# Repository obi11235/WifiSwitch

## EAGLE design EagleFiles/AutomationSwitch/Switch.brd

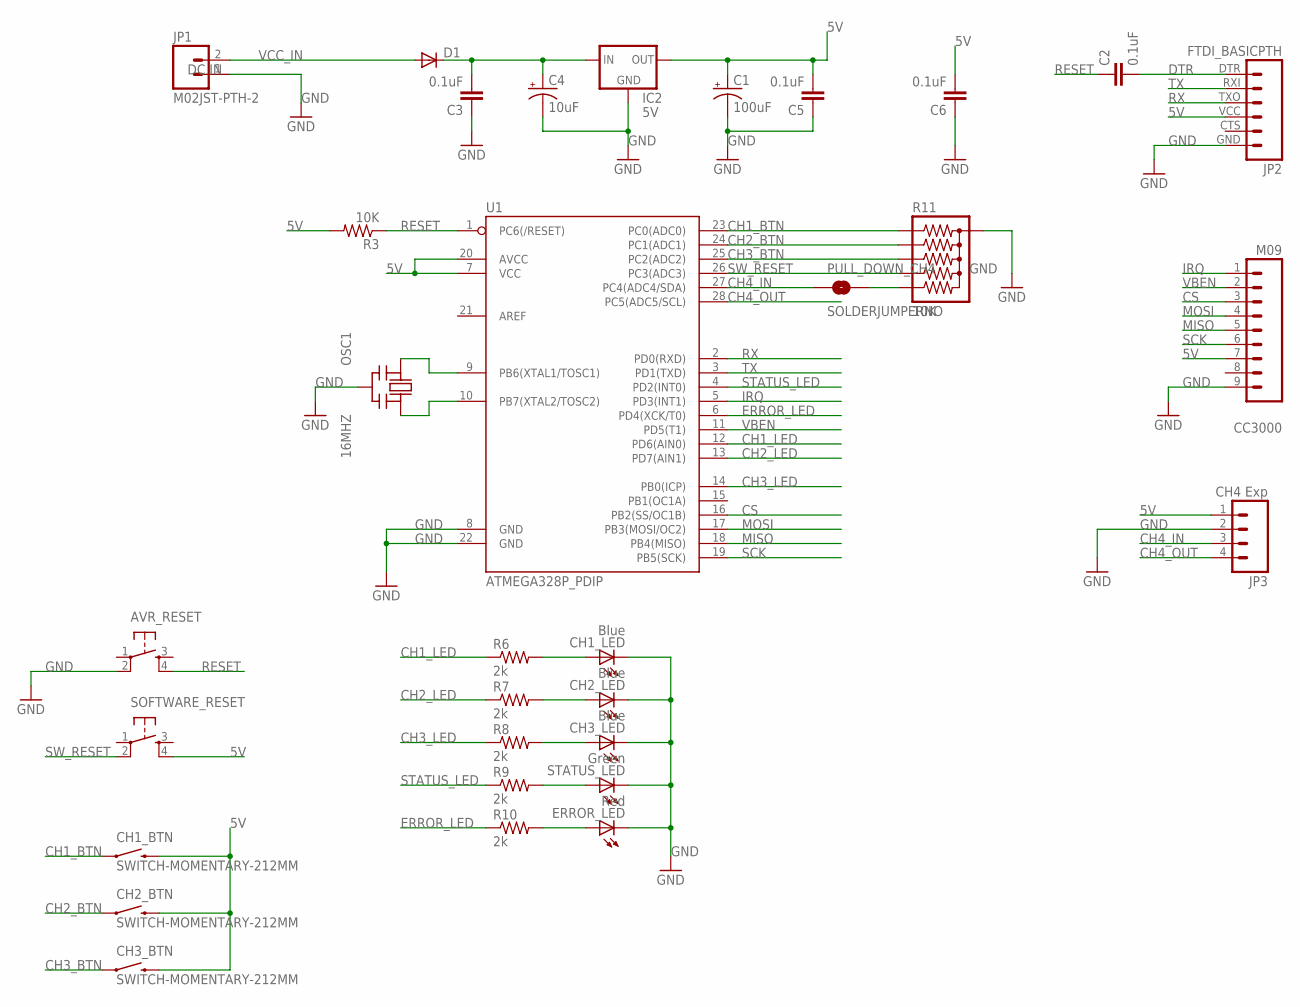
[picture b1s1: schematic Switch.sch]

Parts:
AVR_RESET: TAC_SWITCHPTH; TACTILE-PTH
C1: 100uF; CPOL-RADIAL-100UF-25V
C2, C3, C5, C6: 0.1uF; CAP-PTH-SMALL
C4: 10uF; CPOL-RADIAL-10UF-25V
CC3000: M09; 1X09
CH1_BTN, CH2_BTN, CH3_BTN: SWITCH-MOMENTARY-212MM; TACTILE-PTH-12MM
CH1_LED, CH2_LED, CH3_LED: Blue; LED3MM
D1: DIODEPTH; DIODE-1N4001
ERROR_LED: Red; LED3MM
IC2: 5V; 78XXS
JP1: M02JST-PTH-2; JST-2-PTH
JP2: FTDI_BASICPTH; FTDI_BASIC
JP3: CH4 Exp; JST-4-PTH
OSC1: 16MHZ; CERM_OSC
PULL_DOWN_CH4: SOLDERJUMPERNO; SJ_2S-NO
R3: 10K; 0207/15
R6, R7, R8, R9, R10: 2k; 0207/15
R11: 10K; RPACK-SIP-PTH-5
SOFTWARE_RESET: TAC_SWITCHPTH; TACTILE-PTH
STATUS_LED: Green; LED3MM
U1: ATMEGA328P_PDIP; DIL28-3

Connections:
5V: C1.1 (+), C5.2, C6.2, CC3000.7, CH1_BTN.3 (2), CH2_BTN.3 (2), CH3_BTN.3 (2), IC2.OUT, JP2.VCC (4), JP3.1, R3.2, SOFTWARE_RESET.4, U1.7 (VCC), U1.20 (AVCC)
CH1_BTN: CH1_BTN.1, R11.P$2 (2), U1.23 (PC0(ADC0))
CH1_LED: R6.1, U1.12 (PD6(AIN0))
CH2_BTN: CH2_BTN.1, R11.P$3 (3), U1.24 (PC1(ADC1))
CH2_LED: R7.1, U1.13 (PD7(AIN1))
CH3_BTN: CH3_BTN.1, R11.P$4 (4), U1.25 (PC2(ADC2))
CH3_LED: R8.1, U1.14 (PB0(ICP))
CH4_IN: JP3.3, PULL_DOWN_CH4.1, U1.27 (PC4(ADC4/SDA))
CH4_OUT: JP3.4, U1.28 (PC5(ADC5/SCL))
CS: CC3000.3, U1.16 (PB2(SS/OC1B))
DTR: C2.2, JP2.DTR (1)
ERROR_LED: R10.1, U1.6 (PD4(XCK/T0))
GND: AVR_RESET.2, C1.2 (-), C3.1, C4.2 (-), C5.1, C6.1, CC3000.9, CH1_LED.K (C), CH2_LED.K (C), CH3_LED.K (C), ERROR_LED.K (C), IC2.GND, JP1.1, JP2.GND (6), JP3.2, OSC1.P$2 (GND), R11.P$1 (1), STATUS_LED.K (C), U1.8 (GND), U1.22 (GND)
IRQ: CC3000.1, U1.5 (PD3(INT1))
MISO: CC3000.5, U1.18 (PB4(MISO))
MOSI: CC3000.4, U1.17 (PB3(MOSI/OC2))
unnamed: ERROR_LED.A, R10.2
unnamed: R9.2, STATUS_LED.A
unnamed: CH3_LED.A, R8.2
unnamed: CH2_LED.A, R7.2
unnamed: CH1_LED.A, R6.2
unnamed: OSC1.P$1 (IN), U1.9 (PB6(XTAL1/TOSC1))
unnamed: OSC1.P$3 (OUT), U1.10 (PB7(XTAL2/TOSC2))
unnamed: PULL_DOWN_CH4.2, R11.P$6 (6)
unnamed: C3.2, C4.1 (+), D1.C, IC2.IN
RESET: AVR_RESET.4, C2.1, R3.1, U1.1 (PC6(/RESET))
RX: JP2.TXO (3), U1.2 (PD0(RXD))
SCK: CC3000.6, U1.19 (PB5(SCK))
STATUS_LED: R9.1, U1.4 (PD2(INT0))
SW_RESET: R11.P$5 (5), SOFTWARE_RESET.2, U1.26 (PC3(ADC3))
TX: JP2.RXI (2), U1.3 (PD1(TXD))
VBEN: CC3000.2, U1.11 (PD5(T1))
VCC_IN: D1.A, JP1.2

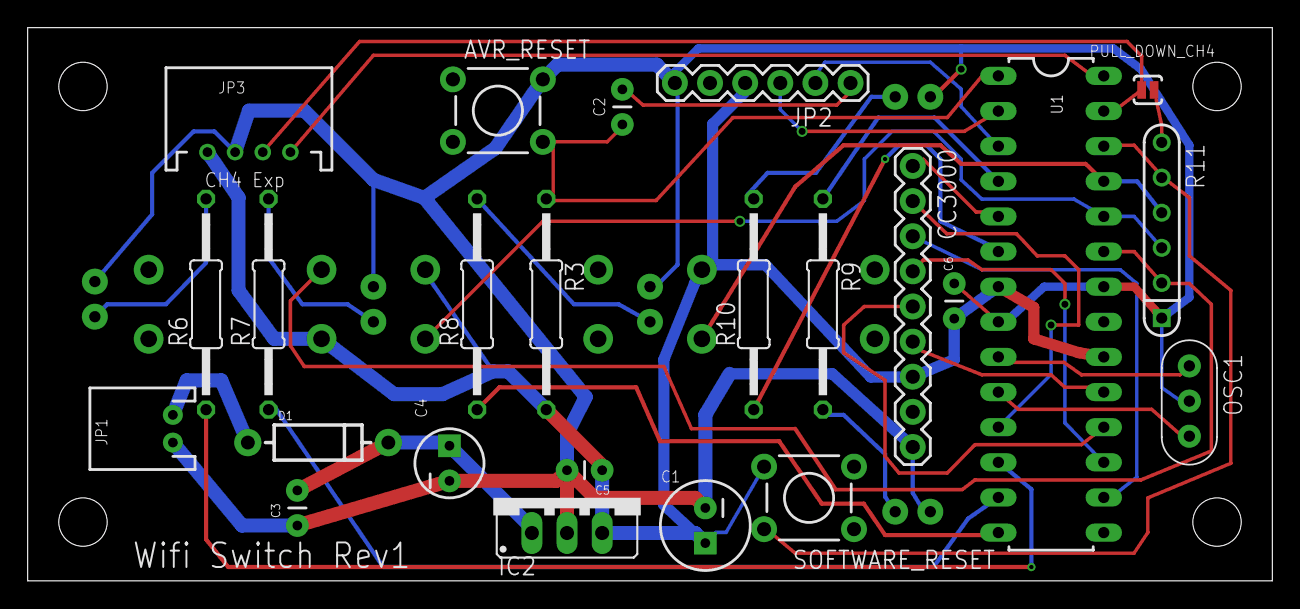
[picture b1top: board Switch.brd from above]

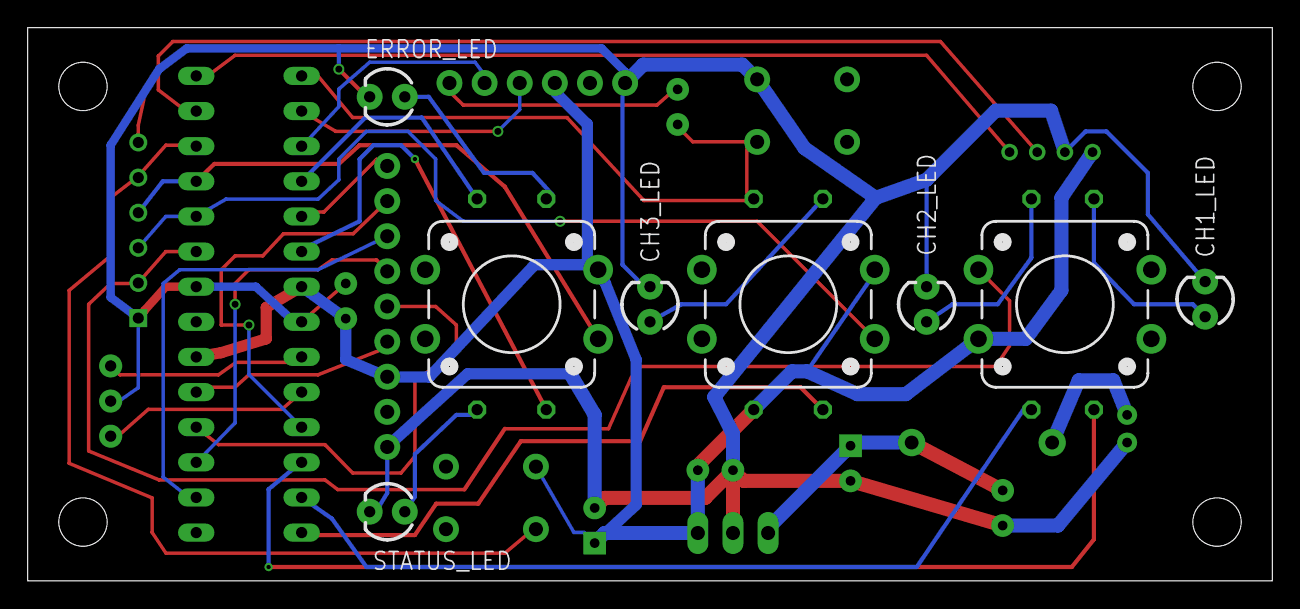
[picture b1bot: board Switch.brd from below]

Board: 2 copper layers, 90.0 x 40.0 mm, 32 parts (8 on the bottom side), 33 nets.

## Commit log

2014-04-23 Baseline
2014-04-23 Reworked routing and power
2014-04-23 Firmware Baseline
2014-04-23 Optimized the Routing
2014-04-23 Optimize Routing
2014-04-24 Rework Traces
2014-04-24 Label Rework
2014-04-26 Adding support to configure settings via serial
2014-04-26 Config loaded from serial port update
2014-04-27 Moved Regulator to fix clearance issues with CC3K Module
2014-04-28 Final Cleanup

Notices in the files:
parts and their libraries:
SparkFun-DigitalIC: Licensing: Creative Commons ShareAlike 4.0 International - https://creativecommons.org/licenses/by-sa/4.0
